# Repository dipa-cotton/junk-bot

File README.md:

# junk-

BOM:

Pics:

inspiration picture:

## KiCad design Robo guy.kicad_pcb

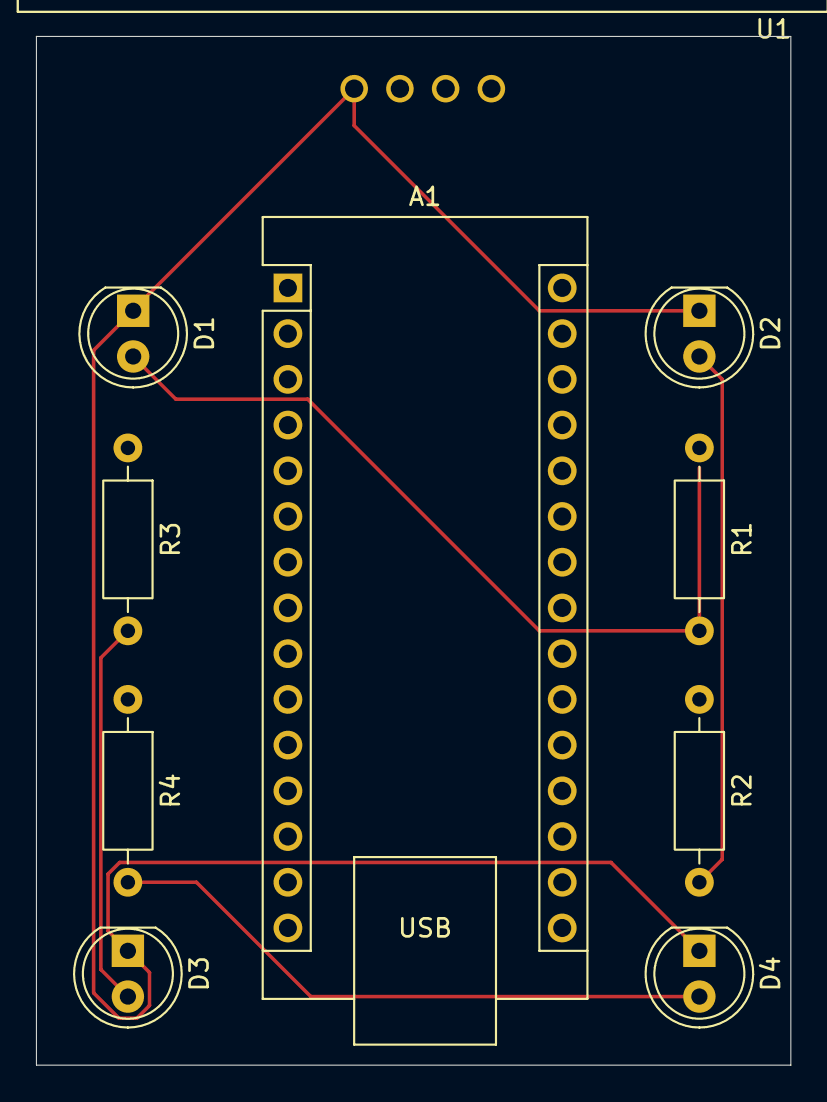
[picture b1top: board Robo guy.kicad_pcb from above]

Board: 2 copper layers, 41.9 x 57.2 mm, 10 parts (0 on the bottom side), 5 nets.

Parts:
A1: Arduino_Nano_ESP32; Arduino_Nano
D1, D2, D3, D4: LED; LED_D5.0mm_IRBlack
R1, R2, R3, R4: R; R_Axial_DIN0207_L6.3mm_D2.5mm_P10.16mm_Horizontal
U1: HC-SR04; XCVR_HC-SR04

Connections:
GND: D1.1 (K), D2.1 (K), D3.1 (K), D4.1 (K), U1.4 (GND)
unnamed: D1.2 (A), R1.2
unnamed: D2.2 (A), R2.2
unnamed: D3.2 (A), R3.2
unnamed: D4.2 (A), R4.2

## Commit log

2026-02-11 Update README with images and BOM section
    Added images and sections to README for better presentation.
